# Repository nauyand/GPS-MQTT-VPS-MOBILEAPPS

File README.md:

# FMB125 → VPS → MQTT (GPS + TPMS)

Server Python menerima data **GPS** (Codec 8 Extended) dan **TPMS via RS232** (Codec 12) dari Teltonika FMB125, lalu meneruskannya ke broker **MQTT Mosquitto**.

| | |
|---|---|
| **Status** | ✅ Pipeline GPS + TPMS berhasil |
| **Terakhir dites** | 8 Oktober 2026 |
| **Kode aktif (v1)** | [`server/gps_server.py`](server/gps_server.py) (di VPS: `/root/gps_server.py`) ✅ sudah jalan |
| **Kode NEXT (v2)** | [`server/gps_server_v2.py`](server/gps_server_v2.py) 🟡 *(belum di-test di VPS/FMB125, perlu deploy di VPS)*, lihat [bagian 10](#10-next-gps_server_v2py) |
| **Aplikasi Android** | [`MyApplication/`](MyApplication/) (GPS Monitor), lihat [bagian 6.5](#65-aplikasi-android-gps-monitor) |

---

## Struktur Repository

```text
.
├── README.md                 ← dokumentasi ini
├── server/                   ← kode Python untuk VPS
│   ├── gps_server.py         ← v1 (sedang jalan di VPS)
│   ├── gps_server_v2.py      ← v2 NEXT (belum di-test di VPS)
│   └── requirements.txt      ← dependensi Python (paho-mqtt)
├── MyApplication/            ← aplikasi Android (buka folder ini di Android Studio)
│   └── app/src/main/java/com/gpsaxius/monitor/MainActivity.kt
└── docs/
    └── app-icon-source.jpeg  ← gambar sumber ikon aplikasi
```

> Untuk mengunduh semua file sekaligus: tombol **Code → Download ZIP** di GitHub.

---

## Daftar Isi

1. [Ringkasan Cepat](#1-ringkasan-cepat)
2. [Arsitektur](#2-arsitektur)
3. [VPS](#3-vps)
4. [FMB125](#4-fmb125)
5. [Protokol & Format Data](#5-protokol--format-data)
6. [MQTT](#6-mqtt)
7. [Menjalankan Project](#7-menjalankan-project)
8. [Troubleshooting](#8-troubleshooting)
9. [Struktur Kode `gps_server.py`](#9-struktur-kode-gps_serverpy)
10. [NEXT: `gps_server_v2.py`](#10-next-gps_server_v2py) *(belum di-test, perlu deploy di VPS)*
11. [Known Issues & Saran Perbaikan](#11-known-issues--saran-perbaikan)
12. [Keamanan](#12-keamanan)
13. [Status & Roadmap](#13-status--roadmap)
14. [Kalimat Kunci untuk Melanjutkan](#14-kalimat-kunci-untuk-melanjutkan)

---

## 1. Ringkasan Cepat

| Item | Nilai |
|---|---|
| VPS IP publik | `202.10.47.206` |
| Hostname | `vps.gpsaxius.id` |
| SSH | `ssh root@202.10.47.206` |
| Kode server | `/root/gps_server.py` |
| Virtualenv | `/root/gps-env` |
| Port GPS (TCP) | `4356` |
| Port MQTT | `1883` (tanpa auth, tanpa TLS) |
| IMEI FMB125 aktif | `352016700616766` |
| Topic GPS | `vehicle/352016700616766/gps` |
| Topic TPMS | `vehicle/352016700616766/tpms` |

> ⚠️ IMEI lama `350544509271766` **tidak dipakai lagi**.

---

## 2. Arsitektur

```text
 TPMS Sensor
     │ RS232
     ▼
┌─────────────────┐
│     FMB125      │  GPS + RS232
└────────┬────────┘
         │ TCP :4356 (internet / GSM)
         ▼
┌─────────────────────────────┐
│  VPS 202.10.47.206          │
│  ├─ gps_server.py (Python)  │
│  └─ Mosquitto MQTT :1883    │
└────────┬────────────────────┘
         │ MQTT
   ┌─────┴──────┐
   ▼            ▼
 Android      SCADA
```

---

## 3. VPS

| Item | Nilai |
|---|---|
| Provider | Rumahweb VPS |
| Hostname | `vps.gpsaxius.id` |
| IP publik | `202.10.47.206` |
| IP privat | `10.0.169.129` |
| OS | Ubuntu 24.04 |
| User | `root` |
| Password | 🔒 **Simpan di password manager, jangan tulis di file ini** |

### Firewall (UFW)

| Port | Fungsi |
|---|---|
| `22/tcp` | SSH |
| `4356/tcp` | FMB125 GPS |
| `1883/tcp` | MQTT |

```bash
ufw status
```

### File penting

| Path | Keterangan |
|---|---|
| `/root/gps_server.py` | Server Python |
| `/root/gps-env/` | Python virtual environment (berisi `paho-mqtt`) |
| `/etc/mosquitto/conf.d/gps.conf` | Konfigurasi Mosquitto |

Isi `gps.conf` saat ini:

```text
listener 1883 0.0.0.0
allow_anonymous true
```

---

## 4. FMB125

### Konfigurasi server di device

| Item | Nilai |
|---|---|
| Device | Teltonika FMB125 |
| IMEI | `352016700616766` |
| Server | `202.10.47.206` |
| Port | `4356` |
| Protocol | TCP |

### Wiring RS232

| Pin FMB125 | Fungsi |
|---|---|
| Pin 3 | RS232 RX |
| Pin 4 | RS232 TX |
| Pin 7 | GND |

```text
Device TX  → FMB125 RX (Pin 3)
Device GND → FMB125 GND (Pin 7)
Device RX  ← FMB125 TX (Pin 4)   # hanya jika komunikasi dua arah
```

> ⚠️ Gunakan level tegangan **RS232**, bukan USB-TTL langsung.

---

## 5. Protokol & Format Data

### 5.1 Alur koneksi TCP

```text
1. FMB125 → [2 byte panjang IMEI][IMEI ASCII]
2. Server → 0x01                         (IMEI diterima)
3. FMB125 → [Preamble 4B][Data Size 4B][Data][CRC 4B]   (berulang)
4. Server → ACK 4 byte (jumlah record / quantity)
```

Byte pertama `Data` = **Codec ID**:

| Codec ID | Codec | Isi | Dikirim ke |
|---|---|---|---|
| `0x8E` | Codec 8 Extended | GPS + IO | `vehicle/{IMEI}/gps` |
| `0x0C` | Codec 12 | Data RS232 (ASCII) | `vehicle/{IMEI}/tpms` (jika diawali `TPMS;`) |

### 5.2 Codec 12 (RS232)

Contoh tes sederhana: device mengirim `HELLO\r\n`, server menampilkan:

```text
[RS232] CODEC 12 TERDETEKSI
[RS232] ASCII : 'HELLO\r\n'
```

ACK Codec 12 = 4 byte quantity.

### 5.3 Format TPMS

```text
TPMS;<ban>;<pressure>;<temperature>;<ban>;<pressure>;<temperature>;...
```

Contoh 8 ban:

```text
TPMS;1;32.50;28.40;2;34.20;29.10;3;31.80;27.60;4;35.10;30.20;5;33.70;28.90;6;32.90;29.50;7;34.80;30.80;8;31.60;27.90
```

| Field | Satuan |
|---|---|
| Pressure | PSI |
| Temperature | °C |

> Parser saat ini **wajib tepat 8 ban** (25 field setelah di-split `;`).

### 5.4 Hasil tes TPMS (8 Okt 2026)

| Ban | Pressure | Temperature |
|---|---:|---:|
| 1 | 32.5 PSI | 28.4 °C |
| 2 | 34.2 PSI | 29.1 °C |
| 3 | 31.8 PSI | 27.6 °C |
| 4 | 35.1 PSI | 30.2 °C |
| 5 | 33.7 PSI | 28.9 °C |
| 6 | 32.9 PSI | 29.5 °C |
| 7 | 34.8 PSI | 30.8 °C |
| 8 | 31.6 PSI | 27.9 °C |

---

## 6. MQTT

### 6.1 Broker

| Item | Nilai |
|---|---|
| Software | Mosquitto |
| Host | `202.10.47.206` (dari luar) / `localhost` (dari VPS) |
| Port | `1883` |
| Username / Password | kosong |
| TLS | OFF |

```bash
systemctl status mosquitto
```

```bash
systemctl restart mosquitto
```

### 6.2 Topic & payload

**GPS** → `vehicle/352016700616766/gps`

```json
{
  "timestamp": "2026-10-08 08:58:42 UTC",
  "latitude": -6.9161633,
  "longitude": 107.5091116,
  "altitude": 699,
  "angle": 266,
  "satellites": 14,
  "speed": 0
}
```

**TPMS** → `vehicle/352016700616766/tpms`

```json
{
  "tire1": { "pressure_psi": 32.5, "temperature_c": 28.4 },
  "tire2": { "pressure_psi": 34.2, "temperature_c": 29.1 },
  "...":   "...",
  "tire8": { "pressure_psi": 31.6, "temperature_c": 27.9 }
}
```

### 6.3 Subscribe (di VPS)

Semua data device:

```bash
mosquitto_sub -h localhost -t 'vehicle/352016700616766/#' -v
```

Hanya GPS:

```bash
mosquitto_sub -h localhost -t 'vehicle/352016700616766/gps' -v
```

Hanya TPMS:

```bash
mosquitto_sub -h localhost -t 'vehicle/352016700616766/tpms' -v
```

### 6.4 Tes MQTT lokal

Terminal 1:

```bash
mosquitto_sub -h localhost -t "test"
```

Terminal 2:

```bash
mosquitto_pub -h localhost -t "test" -m "HELLO MQTT"
```

### 6.5 Aplikasi Android (GPS Monitor)

Kode ada di folder [`MyApplication/`](MyApplication/). Buka folder ini di Android Studio, **bukan** root repo.

| Item | Nilai |
|---|---|
| Nama aplikasi | GPS Monitor |
| Package | `com.gpsaxius.monitor` |
| Kode utama | `MyApplication/app/src/main/java/com/gpsaxius/monitor/MainActivity.kt` |
| Library MQTT | Eclipse Paho `mqttv3` 1.2.5 |
| Min / target SDK | 26 (Android 8.0) / 37 |
| Broker | `tcp://202.10.47.206:1883` (hardcode di `MainActivity.kt`) |
| Topic | `vehicle/352016700616766/gps` dan `vehicle/352016700616766/tpms` (hardcode) |

**Fitur:**

- Status koneksi MQTT dengan auto-reconnect
- GPS: kecepatan, satelit, lat/lon, ketinggian, arah, waktu GPS, dan tombol **buka di Google Maps**
- TPMS 8 ban: tekanan (PSI) dan temperatur (°C), dengan warna status NORMAL / PERINGATAN / BAHAYA
- Alarm: notifikasi per ban saat kritis dan suara TTS bahasa Indonesia
- Pengaturan batas alarm (tekanan min/maks, temperatur maks), tersimpan di HP

**Batas alarm default:**

| Parameter | Default |
|---|---|
| Tekanan minimum | 90 PSI |
| Tekanan maksimum | 120 PSI |
| Temperatur maksimum | 80 °C |

> ⚠️ Peringatan dan bahaya: PERINGATAN muncul 5 PSI sebelum batas tekanan atau 10 °C sebelum batas temperatur. Dengan data tes (32–35 PSI), semua ban akan tampil **BAHAYA**. Sesuaikan lewat tombol pengaturan alarm di aplikasi.

**Catatan aplikasi (belum diperbaiki):**

- Alarm hanya jalan saat aplikasi terbuka di layar (belum ada Foreground Service)
- Di Android 15+, tampilan bisa tertutup status bar atau tombol navigasi (belum ada penanganan edge-to-edge insets)
- Saat layar diputar, data di layar kosong sampai pesan MQTT berikutnya masuk

**Tes manual dengan aplikasi MQTT lain:** isi broker `202.10.47.206`, port `1883`, username dan password kosong, TLS OFF, lalu subscribe `vehicle/352016700616766/#`.

✅ GPS dan TPMS sudah berhasil diterima di HP.

---

## 7. Menjalankan Project

**1. Login ke VPS**

```bash
ssh root@202.10.47.206
```

**2. Aktifkan environment**

```bash
source /root/gps-env/bin/activate
```

**3. Cek syntax** (tidak ada output = OK)

```bash
python3 -m py_compile /root/gps_server.py
```

**4. Jalankan server**

```bash
/root/gps-env/bin/python /root/gps_server.py
```

Output yang diharapkan: `[SERVER] Listening on 0.0.0.0:4356`

**5. Buka terminal SSH kedua, subscribe MQTT**

```bash
mosquitto_sub -h localhost -t 'vehicle/352016700616766/#' -v
```

**6. Nyalakan FMB125**, pastikan device mengarah ke `202.10.47.206:4356`.

> Server masih dijalankan manual. Kalau terminal SSH ditutup, server ikut berhenti (belum ada `systemd`).

---

## 8. Troubleshooting

### Port 4356 sudah dipakai

```bash
ss -ltnp | grep :4356
```

Cari PID-nya, contoh `users:(("python3",pid=27647,fd=3))`, lalu matikan:

```bash
kill 27647
```

Kalau tidak berhenti:

```bash
kill -9 27647
```

Setelah itu jalankan server lagi (langkah 4 di bagian 7).

### Data MQTT tidak muncul

Cek berurutan:

```bash
systemctl status mosquitto
```

```bash
ss -ltnp | grep :1883
```

```bash
ufw status
```

```bash
mosquitto_sub -h localhost -t 'vehicle/352016700616766/#' -v
```

Cek juga:

- Apakah log server menampilkan `[IMEI] 352016700616766`? Kalau tidak, FMB125 belum terkoneksi (cek APN/GPRS dan setting server di device).
- Apakah muncul `[MQTT] ... published → ...`? Kalau tidak, paket belum ter-parse.
- TPMS tidak muncul padahal `[RS232] ASCII` terlihat? Cek format, harus tepat 25 field (lihat log `[TPMS] Format tidak sesuai`).

---

## 9. Struktur Kode `gps_server.py`

| Fungsi | Tugas |
|---|---|
| `main()` | Listen di `0.0.0.0:4356`, membuat 1 thread per koneksi |
| `client_worker()` | Membungkus `handle_client` dengan try/except, lalu menutup socket |
| `handle_client()` | Membaca IMEI, kirim `0x01`, loop baca frame (preamble, size, data, CRC) |
| `process_packet()` | Routing berdasarkan Codec ID (`0x8E` / `0x0C`) |
| `parse_codec_8_extended()` | Parse GPS dan IO, publish GPS, kirim ACK |
| `parse_codec_12()` | Parse RS232, parse TPMS, publish TPMS, kirim ACK |
| `read_exact()` | Membaca tepat N byte dari socket |

### Konfigurasi di dalam kode

| Variabel | Default | Fungsi |
|---|---|---|
| `HOST`, `PORT` | `0.0.0.0`, `4356` | Alamat listen TCP |
| `MQTT_HOST`, `MQTT_PORT` | `localhost`, `1883` | Broker MQTT |
| `SHOW_RAW_HEX` | `False` | `True` = tampilkan hex mentah setiap paket |
| `DISPLAY_IO_IDS` | `[]` | IO ID yang ditampilkan di log, misalnya `[239, 240, 21]` |

IO ID yang pernah terlihat dari FMB125: `239, 240, 21, 200, 69, 181, 182, 66, 67, 68, 201, 241, 16`.

Dependensi: `paho-mqtt` (terpasang di `/root/gps-env`, daftar ada di [`server/requirements.txt`](server/requirements.txt)). Untuk install di VPS baru:

```bash
/root/gps-env/bin/pip install -r requirements.txt
```

---

## 10. NEXT: `gps_server_v2.py`

> 🟡 **Status: (belum di-test di VPS / FMB125 asli, perlu deploy di VPS)**
>
> Sudah lolos tes simulator di luar VPS (lihat 10.3). File v1 `gps_server.py` **tidak diubah** dan tetap bisa dipakai sebagai cadangan.

### 10.1 Apa yang berubah

| # | Perubahan | Mengatasi Known Issue |
|---|---|---|
| 1 | IMEI disimpan per koneksi (class `Session`), bukan variabel global | #1 |
| 2 | Validasi preamble `00 00 00 00` dan CRC-16/IBM. Paket rusak dibalas ACK `0` supaya device mengirim ulang | #2 |
| 3 | Socket timeout `SOCKET_TIMEOUT = 600` detik | #3 |
| 4 | Buffer RS232 per koneksi: data dikumpulkan sampai ada newline | #4 |
| 5 | TPMS jumlah ban dinamis (jumlah field kelipatan 3) | #5 |
| 6 | Payload GPS ditambah `"valid": true/false` (berdasarkan `satellites > 0`) | #6 |
| 7 | Variabel loop dirapikan, parser memakai class `Reader` dengan cek panjang | #7 |
| 8 | Error parsing tidak memutus koneksi. Paket tetap di-ACK agar device tidak mengirim ulang terus | — |
| 9 | MQTT `connect_async` dan auto-reconnect, kompatibel paho-mqtt 1.x dan 2.x | — |
| 10 | Log memakai waktu dan IMEI: `2026-11-02 03:22:44 [352016700616766] [GPS] ...` | — |
| 11 | GPS di-publish **setelah** record selesai di-parse lengkap | — |

**Yang tidak berubah:** port `4356`, setting FMB125, topic MQTT, format payload TPMS. Aplikasi di HP tidak perlu diubah.

### 10.2 Konfigurasi baru di `gps_server_v2.py`

| Variabel | Default | Keterangan |
|---|---|---|
| `SOCKET_TIMEOUT` | `600` | Detik tanpa data sebelum koneksi ditutup. Harus **lebih besar** dari interval kirim FMB125 saat diam/parkir |
| `CHECK_CRC` | `True` | `False` = matikan cek CRC (hanya untuk debug) |
| `RS232_REQUIRE_NEWLINE` | `True` | `True` = tunggu `\n` sebelum proses. `False` = langsung proses setiap paket (perilaku v1) |
| `MAX_PACKET_SIZE` | `65536` | Batas ukuran 1 paket |

> ⚠️ **Penting soal `RS232_REQUIRE_NEWLINE`:** perangkat TPMS harus mengirim `\r\n` di akhir setiap baris. Cek log v1: kalau `[RS232] HEX` berakhiran `0d 0a`, berarti aman. Kalau tidak, set `RS232_REQUIRE_NEWLINE = False`. Tanda masalahnya, log v2 terus menampilkan `Menunggu sisa data (belum ada newline)` dan TPMS tidak pernah publish.

### 10.3 Hasil tes simulator (2 Nov 2026, bukan di VPS)

Dites dengan Mosquitto asli dan simulator FMB125 (paket Codec 8E dan Codec 12 dengan CRC):

| Tes | Hasil |
|---|---|
| CRC-16 cocok dengan contoh dokumentasi Teltonika (`C7CF`) | ✅ |
| 2 device bersamaan, data masuk ke topic IMEI masing-masing | ✅ |
| GPS: lat/lon benar, `valid: true` | ✅ |
| TPMS 8 ban dalam 1 paket | ✅ |
| TPMS terpotong di 2 paket, digabung lalu publish 1× | ✅ |
| TPMS 6 ban (device lain, buffer terpisah) | ✅ |
| TPMS format salah tidak di-publish | ✅ |
| CRC salah dibalas ACK 0, tidak di-publish | ✅ |
| GPS `satellites = 0` menghasilkan `valid: false` | ✅ |
| Paket terpotong tetap di-ACK dan koneksi tetap hidup | ✅ |
| Koneksi diam ditutup setelah timeout | ✅ |

**Belum dites:** FMB125 asli, sinyal GSM nyata, TPMS asli, versi paho-mqtt di VPS.

### 10.4 Cara deploy ke VPS *(belum dilakukan)*

**1. Upload file** (dari komputer Windows, di dalam folder `server/` repo ini)

```bash
scp gps_server_v2.py root@202.10.47.206:/root/
```

**2. Login dan cek syntax**

```bash
ssh root@202.10.47.206
```

```bash
/root/gps-env/bin/python -m py_compile /root/gps_server_v2.py
```

**3. Hentikan v1** (tekan `Ctrl+C` di terminal v1, atau cari PID-nya)

```bash
ss -ltnp | grep :4356
```

```bash
kill <PID>
```

**4. Jalankan v2**

```bash
/root/gps-env/bin/python /root/gps_server_v2.py
```

Output yang diharapkan: `[SERVER] v2 listening on 0.0.0.0:4356`

**5. Terminal kedua, pantau MQTT**

```bash
mosquitto_sub -h localhost -t 'vehicle/352016700616766/#' -v
```

### 10.5 Checklist tes di VPS

- [ ] Server v2 jalan tanpa error
- [ ] Log menampilkan `[IMEI] 352016700616766 accepted`
- [ ] Tidak ada `[CRC] TIDAK COCOK` pada paket normal
- [ ] GPS muncul di MQTT dan ada field `"valid"`
- [ ] TPMS 8 ban muncul di MQTT
- [ ] HP Android tetap menerima GPS dan TPMS
- [ ] FMB125 reconnect normal setelah koneksi putus atau timeout
- [ ] Biarkan jalan ≥1 jam, tidak ada error berulang

Kalau semua ✅, ubah status di README ini menjadi "sudah dites" dan jadikan v2 versi utama (lanjut Tahap B: `systemd`).

### 10.6 Rollback (kembali ke v1)

Hentikan v2 (`Ctrl+C`), lalu jalankan:

```bash
/root/gps-env/bin/python /root/gps_server.py
```

---

## 11. Known Issues & Saran Perbaikan

Hasil review kode **v1** (`gps_server.py`). Sistem saat ini **berjalan untuk 1 device**, tapi poin di bawah perlu dibereskan sebelum production atau multi-vehicle.

> Poin #1–#7 sudah diperbaiki di **v2** *(belum di-test, perlu deploy di VPS)*. Poin #8 menunggu Tahap B.

| # | Prioritas | Masalah | Dampak | Saran |
|---|---|---|---|---|
| 1 | 🔴 Tinggi | `CURRENT_IMEI` adalah variabel **global** yang dipakai bersama oleh semua thread | Dengan ≥2 device, data device A bisa ter-publish ke topic IMEI device B | Simpan IMEI per koneksi lalu oper sebagai parameter ke `process_packet` dan parser |
| 2 | 🟠 Sedang | CRC dan preamble tidak divalidasi | Paket rusak tetap diproses dan di-ACK | Validasi CRC-16/IBM dan pastikan preamble = `00 00 00 00` |
| 3 | 🟠 Sedang | Socket tanpa timeout | Koneksi GSM yang putus diam-diam membuat thread menggantung selamanya | `conn.settimeout(300)` atau aktifkan TCP keepalive |
| 4 | 🟠 Sedang | Data RS232 tidak di-buffer | Baris TPMS yang terpecah ke 2 paket Codec 12 gagal di-parse | Buffer per koneksi, proses data setelah ketemu `\r\n` |
| 5 | 🟡 Rendah | Parser TPMS wajib tepat 8 ban (`len(parts) == 25`) | Kendaraan dengan jumlah ban lain ditolak | Cek `(len(parts) - 1) % 3 == 0` agar jumlah ban dinamis |
| 6 | 🟡 Rendah | GPS tetap di-publish saat `satellites == 0` | Koordinat 0 atau posisi lama terkirim seolah valid | Tambahkan field `"valid": satellites > 0` |
| 7 | 🟡 Rendah | Variabel loop `i` dipakai ganda (loop TPMS di dalam loop Codec 12) | Belum menimbulkan bug, tapi membingungkan | Ganti nama variabel loop TPMS, misalnya `t` |
| 8 | 🟡 Rendah | Server dijalankan manual | Mati saat SSH ditutup atau VPS reboot | Buat service `systemd` |

---

## 12. Keamanan

⚠️ Konfigurasi saat ini **hanya untuk testing**:

- MQTT `1883` terbuka ke internet dengan `allow_anonymous true`. Siapa pun bisa **membaca lokasi kendaraan secara real-time** (subscribe `vehicle/#`) dan **mengirim data palsu**.
- Port `4356` menerima koneksi dari IMEI apa pun (tidak ada whitelist).
- Password VPS **jangan** disimpan di notes, cloud, atau repo. Gunakan password manager. Pertimbangkan login SSH dengan key dan matikan login password.

Rencana hardening:

```text
MQTT username/password + ACL per topic + TLS di port 8883
Whitelist IMEI di gps_server.py
SSH key-only login
```

---

## 13. Status & Roadmap

### Selesai ✅

- [x] VPS Rumahweb aktif dan SSH berhasil
- [x] Python environment dan GPS server
- [x] Koneksi TCP FMB125
- [x] Parser Codec 8 Extended (GPS)
- [x] Parser Codec 12 (RS232)
- [x] Mosquitto MQTT
- [x] GPS → MQTT
- [x] TPMS → RS232 → FMB125 → Python → MQTT
- [x] Android menerima MQTT
- [x] Pressure dan temperature terbaca, 8 ban berhasil dites

### Belum dikerjakan ⏳

Urutan yang disarankan:

| Tahap | Pekerjaan |
|---|---|
| **A** | 🟡 **NEXT:** refactor sudah dibuat sebagai `gps_server_v2.py` *(belum di-test, perlu deploy di VPS)*, lihat [bagian 10](#10-next-gps_server_v2py) |
| **B** | Service `systemd` untuk `gps_server.py` (auto-start dan auto-restart) |
| **C** | MQTT authentication, ACL, TLS, port 8883 |
| **D** | Penyimpanan database dan dashboard/web |
| **E** | Monitoring online/offline device (MQTT LWT / topic `vehicle/{IMEI}/status`) |
| — | Integrasi Android khusus TPMS |
| — | Multi-FMB125 / multi-vehicle (butuh tahap A dulu) |

---

## 14. Kalimat Kunci untuk Melanjutkan

Tempel kalimat ini saat membuka chat baru:

> **Lanjutkan project FMB125 → VPS → MQTT. VPS 202.10.47.206, Python `/root/gps_server.py`, FMB125 IMEI 352016700616766, TCP port 4356, Mosquitto port 1883. GPS sudah berhasil ke MQTT dan TPMS Codec 12 juga sudah berhasil ke topic `vehicle/352016700616766/tpms`. Refactor `gps_server_v2.py` sudah dibuat (lolos tes simulator, belum di-test di VPS, perlu deploy). Lihat README.md bagian 10 (NEXT) dan Roadmap.**

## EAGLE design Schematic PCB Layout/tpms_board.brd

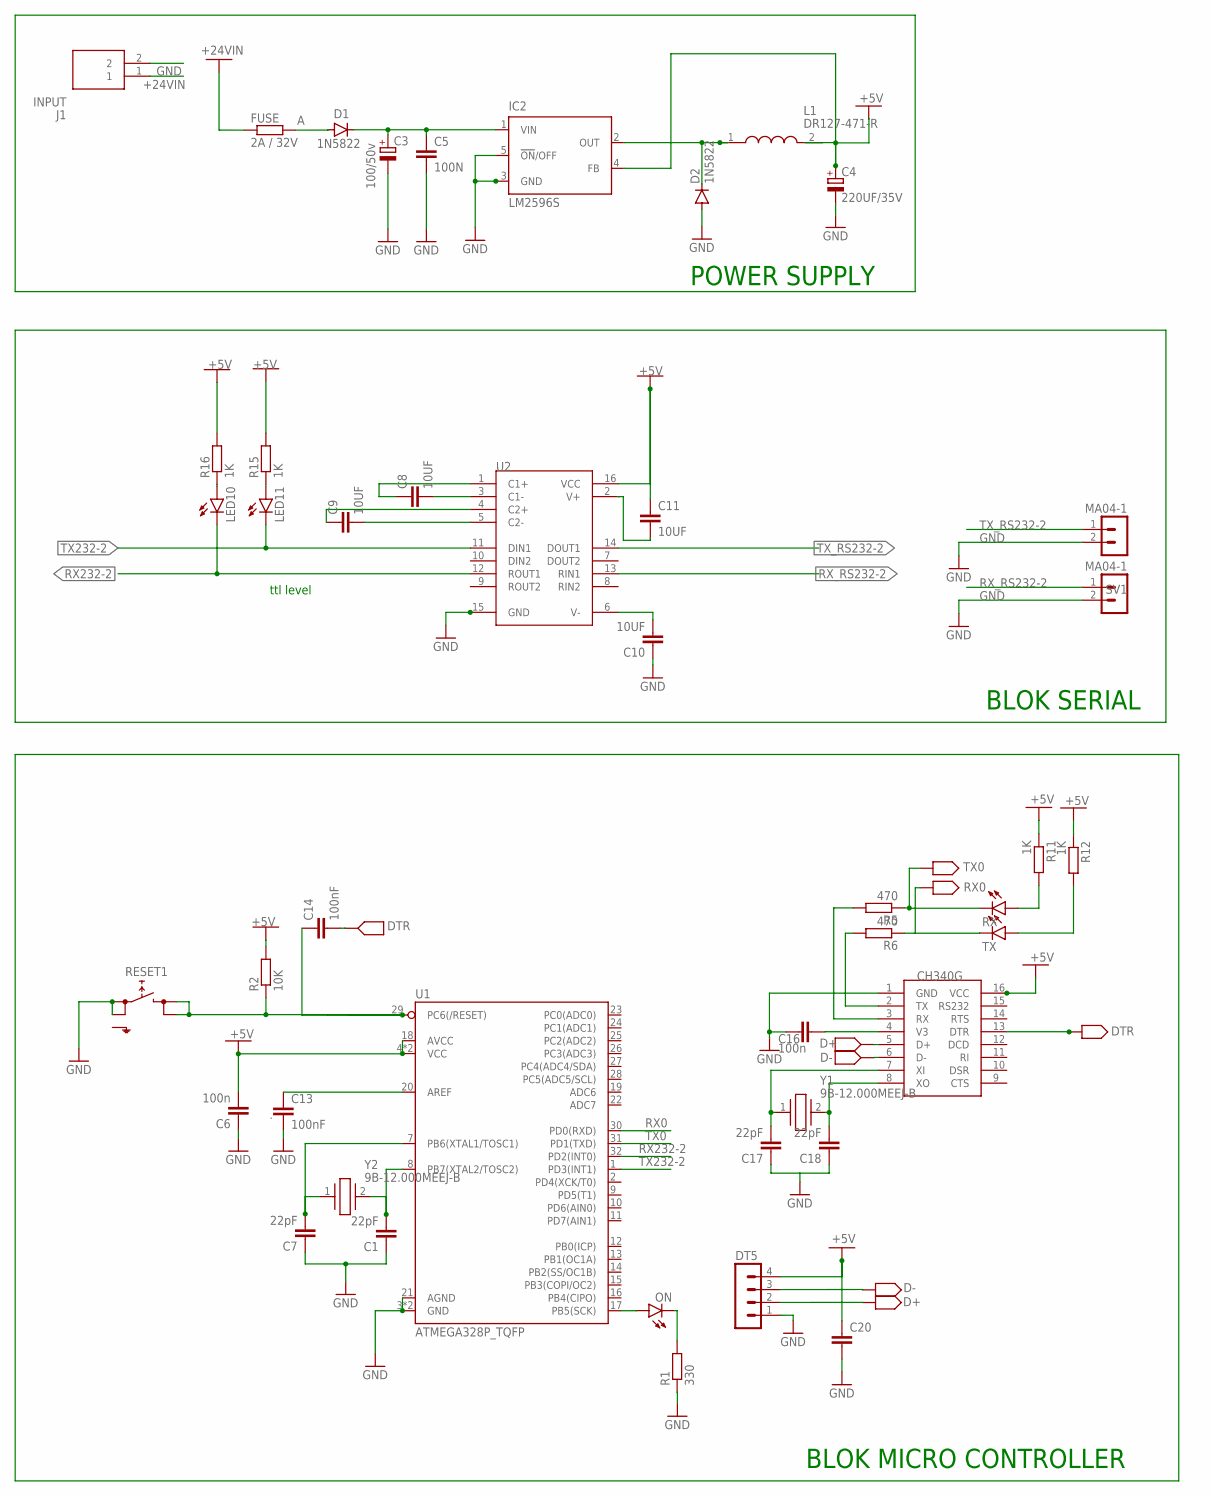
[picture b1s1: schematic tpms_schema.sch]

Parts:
C1, C7, C17, C18: 22pF; C0805
C3: 100/50v; PANASONIC_G
C4: 220UF/35V; PANASONIC_G
C5: 100N; C0805
C6, C16: 100n; C0805
C8, C9, C10, C11: 10UF; C0805
C13, C14: 100nF; C0805
C20: 1uF; C0805
D1, D2: 1N5822; MELF-MLL41
DT5: MA04-1
FUSE: 2A / 32V; R1206
IC2: LM2596S; TO263-5
J1: INPUT; 691305330002
L1: DR127-471-R; INDPM125125X800N
LED10, LED11: LEDCHIPLED_0805; CHIPLED_0805
ON: LEDCHIP-LED0805; CHIP-LED0805
R1: 330; R0805
R2: 10K; R0805
R5, R6: 470; R0805
R11, R12, R15, R16: 1K; R0805
RESET1: SKHMPSE010; SKHMPXE010
RX: LEDCHIP-LED0805; CHIP-LED0805
SV1, SV2: MA04-1
TX: LEDCHIP-LED0805; CHIP-LED0805
U1: ATMEGA328P_TQFP; TQFP32-08
U2: RF-MAX232D; SOIC16-1.27-10X3.9MM
U$1: CH340G; SOIC16
Y1, Y2: 9B-12.000MEEJ-B; 9B12000MEEJB

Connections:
+5V: C4.+, C6.2, C11.1, C20.1, DT5.4, IC2.4 (FB), L1.2, R2.2, R11.1, R12.1, R15.2, R16.2, U1.4 (VCC), U1.6 (VCC), U1.18 (AVCC), U2.16 (VCC), U$1.16 (VCC)
+24VIN: FUSE.1, J1.1
A: D1.A, FUSE.2
D+: DT5.2, U$1.5 (D+)
D-: DT5.3, U$1.6 (D-)
DTR: C14.2, U$1.13 (DTR)
GND: C1.1, C3.-, C4.-, C5.2, C6.1, C7.1, C10.1, C13.2, C16.1, C17.1, C18.1, C20.2, D2.A, DT5.1, IC2.3 (GND), IC2.5 (!ON!/OFF), J1.2, R1.1, RESET1.1 (1.1), RESET1.2 (1.2), SV1.2, SV2.2, U1.3 (GND), U1.5 (GND), U1.21 (AGND), U2.15 (GND), U$1.1 (GND)
unnamed: C9.2, U2.5 (C2-)
unnamed: C9.1, U2.4 (C2+)
unnamed: ON.A, U1.17 (PB5(SCK))
unnamed: ON.C, R1.2
unnamed: C13.1, U1.20 (AREF)
unnamed: R11.2, RX.A
unnamed: R12.2, TX.A
unnamed: C16.2, U$1.4 (V3)
unnamed: C17.2, U$1.7 (XI), Y1.1
unnamed: C18.2, U$1.8 (XO), Y1.2
unnamed: R5.2, U$1.3 (RX)
unnamed: R6.2, U$1.2 (TX)
unnamed: LED10.A, R16.1
unnamed: C8.2, U2.3 (C1-)
unnamed: C8.1, U2.1 (C1+)
unnamed: D2.C, IC2.2 (OUT), L1.1
unnamed: LED11.A, R15.1
unnamed: C10.2, U2.6 (V-)
unnamed: C11.2, U2.2 (V+)
unnamed: C3.+, C5.1, D1.C, IC2.1 (VIN)
PB6: C7.2, U1.7 (PB6(XTAL1/TOSC1)), Y2.1
PB7: C1.2, U1.8 (PB7(XTAL2/TOSC2)), Y2.2
RESET: C14.1, R2.1, RESET1.3 (2.1), RESET1.4 (2.2), U1.29 (PC6(/RESET))
RX0: R6.1, TX.C, U1.30 (PD0(RXD))
RX232-2: LED10.C, U1.32 (PD2(INT0)), U2.12 (ROUT1)
RX_RS232-2: SV2.1, U2.13 (RIN1)
TX0: R5.1, RX.C, U1.31 (PD1(TXD))
TX232-2: LED11.C, U1.1 (PD3(INT1)), U2.11 (DIN1)
TX_RS232-2: SV1.1, U2.14 (DOUT1)

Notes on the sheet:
ttl level
POWER SUPPLY
BLOK SERIAL
BLOK MICRO CONTROLLER

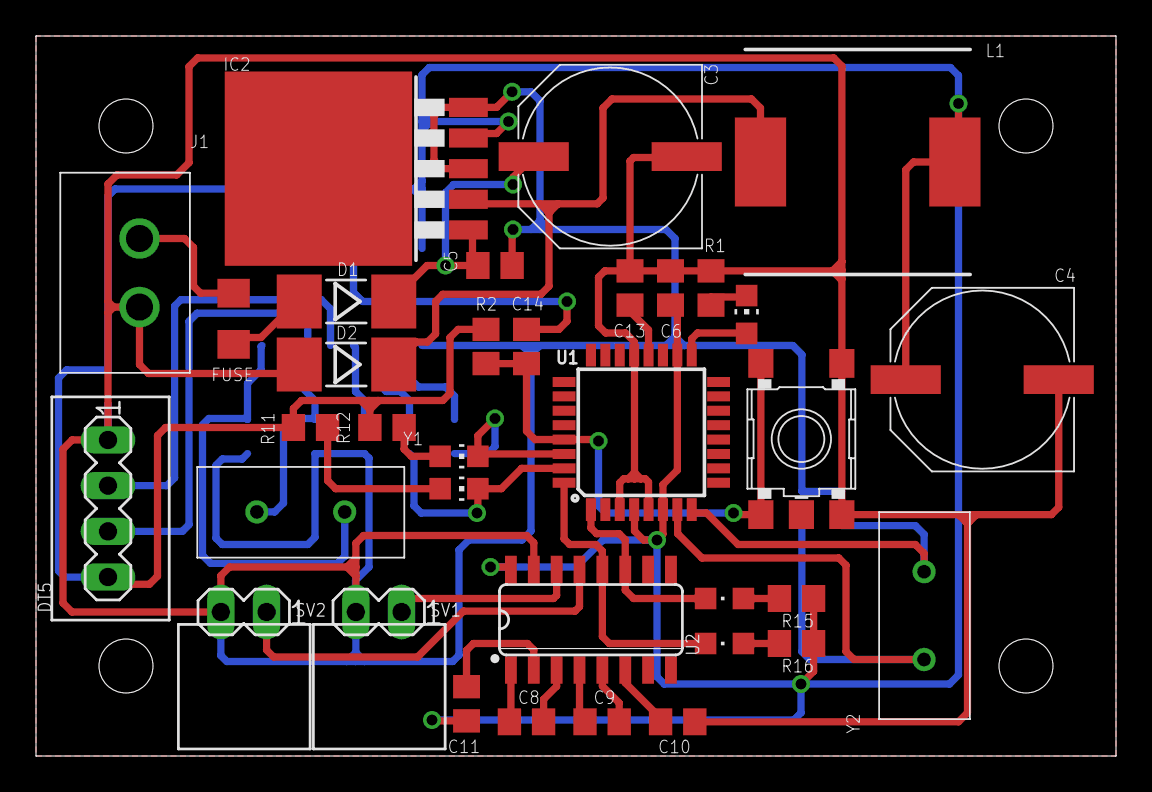
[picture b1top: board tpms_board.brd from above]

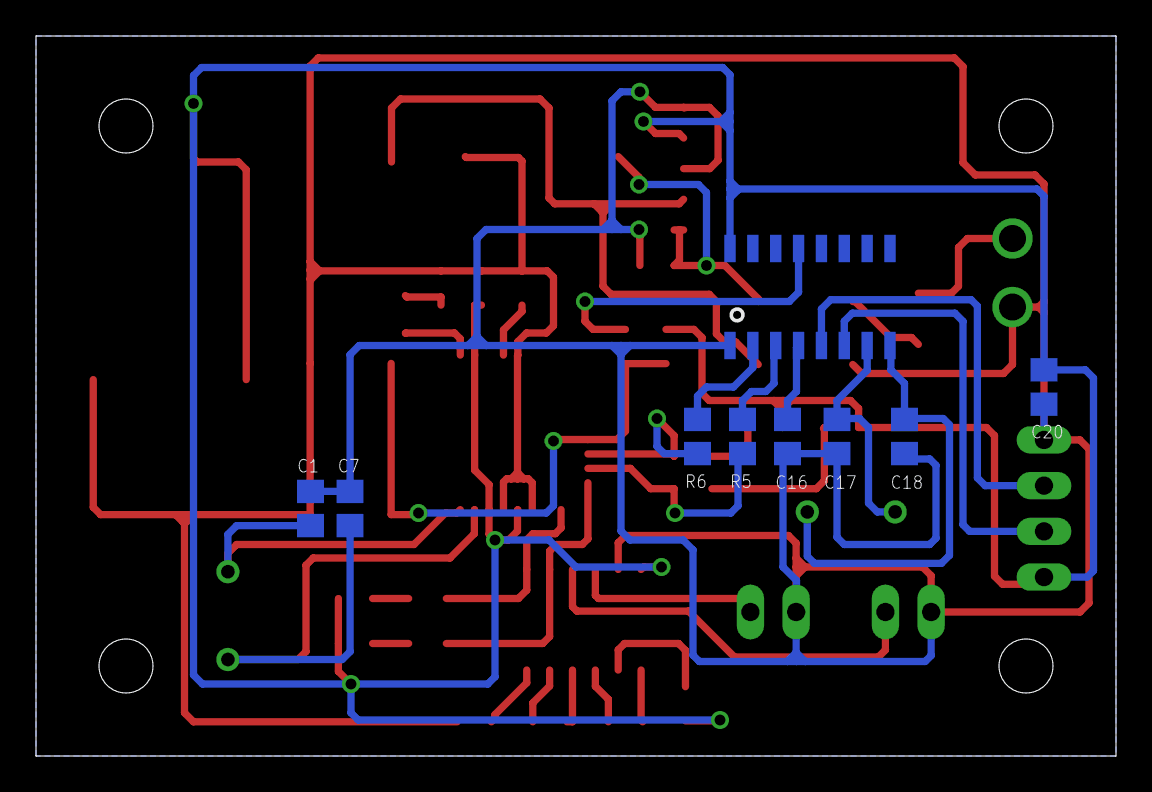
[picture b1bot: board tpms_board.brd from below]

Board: 2 copper layers, 60.0 x 40.0 mm, 44 parts (9 on the bottom side), 36 nets.

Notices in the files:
parts and their libraries:
SparkFun-IC-Microcontroller: Licensing: Creative Commons ShareAlike 4.0 International - https://creativecommons.org/licenses/by-sa/4.0
